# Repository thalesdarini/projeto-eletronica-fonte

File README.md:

# Projeto da Fonte de Tensão

## Objetivos

Projetar uma fonte de tensão ajustável que varie de 3V a 12V e que suporte uma corrente de pelo menos 100mA.

**Aluno:** Thales Darini Souza - 10747562

## Circuito no Falstad
**[Link do circuito no Falstad](http://tinyurl.com/y722ua49)**

**[Link do vídeo explicativo](https://youtu.be/_xOmkor7MkY)**

## Componentes utilizados

|Nome|Especificações|Descrição|Preço|
|---|---|---|---|
|Transformador|12V+12V 300mA|Utilizado para converter a tensão da tomada de 127V AC para 24V AC. Com esses 24V de pico é possível garantir que o zener fique constantemente ligado, considerando as quedas de tensão e ainda com uma boa margem de segurança.|[R$ 16,45](https://www.baudaeletronica.com.br/transformador-trafo-12v-12v-300ma-110-220vac.html)|
|Diodos|1N4001|Utilizados para formar a ponte de diodos a fim de aproveitar ambos os ciclos negativo e positivo da corrente alternada. Juntamente com o capacitor, a ponte retificadora é responsável por transformar a tensão de AC para CC e retificá-la.|[4x R$ 0,14 = R$ 0,56](https://www.baudaeletronica.com.br/diodo-1n4001.html)| 
|Diodo Zener|BZX55C 13V|A função deste zener será manter uma tensão constante de 13V entre seus polos, que, com a ajuda de um potenciômetro, poderá ser ajustada no intervalo de 3V a 12V para a carga, como desejado.|[R$ 0,09](https://www.baudaeletronica.com.br/diodo-zener-bzx55c-13v-0-5w.html)|
|Capacitor Eletrolítico|330uF 35V|O capacitor armazena energia ao longo de cada oscilação para garantir que sempre seja fornecida energia ao restante do circuito. Foi escolhido o de 330uF para a tensão de ~24V provinda do transformador por ser suficiente para manter o zener ligado o tempo todo sem oscilações.|[R$ 0,34](https://www.baudaeletronica.com.br/capacitor-eletrolitico-330uf-35v.html)|
|Potenciômetro|10K|É com o potenciômetro que ajustamos a tensão final fornecida à carga, variando de 3V a 12V.|[R$ 1,46](https://www.baudaeletronica.com.br/potenciometro-linear-de-10k-10000.html)|
|Resistor|2K2 (1/4W)|Este resistor regula a corrente que passa pelo zener, mantendo-a abaixo de 5mA.|[R$ 0,08](https://www.baudaeletronica.com.br/resistor-2k2-5-1-4w.html)|
|Resistor|5K6 (1/4W)|A função deste resistor é limitar a tensão mínima fornecida à carga em 3V quando o potênciometro está no seu limite inferior.|[R$ 0,08](https://www.baudaeletronica.com.br/resistor-5k6-5-1-4w.html)|
|Resistor|560R (1/4W)|Usado para ligar o LED difuso no final do circuito. Especificação do fabricante para uma tensão de 12V.|[R$ 0,08](https://www.baudaeletronica.com.br/resistor-560r-5-1-4w.html)|
|LED difuso|3mm verde|Conectado ao fim do circuito para indicar que a fonte está ligada. Além disso, a intensidade de seu brilho é diretamente proporcional à tensão que passa pela carga, que varia de 3V a 12V.|[R$ 0,24](https://www.baudaeletronica.com.br/led-difuso-3mm-verde.html)|
|Transistor NPN|BC635|Este transistor é usado para manter a tensão desejada de até 12V na carga a partir da tensão provinda do zener e do potenciômetro e, ao mesmo tempo, permitir a passagem da corrente desejada de 100mA.|[R$ 0,33](https://www.baudaeletronica.com.br/transistor-npn-bc635.html)|
|**Total**|||**R$ 19,71**|

## Esquemático no Eagle 

## PCB no Eagle

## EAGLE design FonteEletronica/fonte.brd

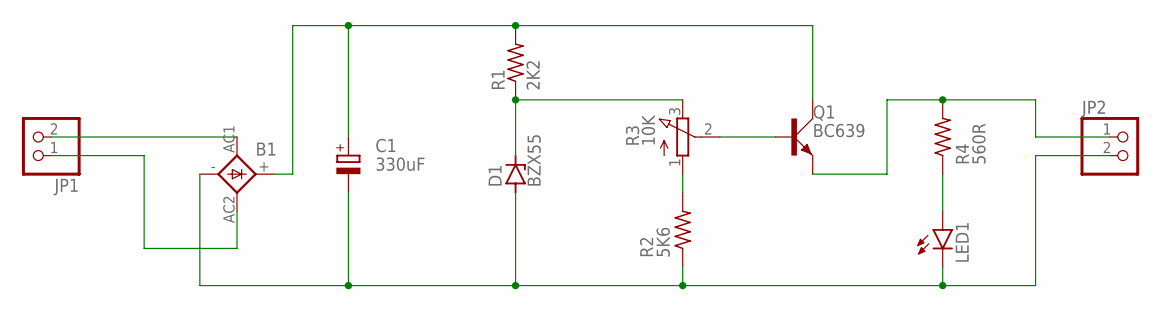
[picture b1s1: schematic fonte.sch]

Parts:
B1: 1KAB
C1: 330uF; E3,5-10
D1: BZX55; DO35Z10
JP1, JP2: PINHD-1X2; 1X02
LED1: LED3MM
Q1: BC639; SOT54D
R1: 2K2; 0309/12
R2: 5K6; 0309/12
R3: 10K; 3RP/1610N
R4: 560R; 0309/12

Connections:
unnamed: B1.AC1, JP1.2
unnamed: B1.AC2, JP1.1
unnamed: B1.+, C1.+, Q1.C, R1.2
unnamed: B1.-, C1.-, D1.A, JP2.2, LED1.K (C), R2.1
unnamed: D1.C, R1.1, R3.3 (E)
unnamed: R2.2, R3.1 (A)
unnamed: Q1.B, R3.2 (S)
unnamed: JP2.1, Q1.E, R4.2
unnamed: LED1.A, R4.1

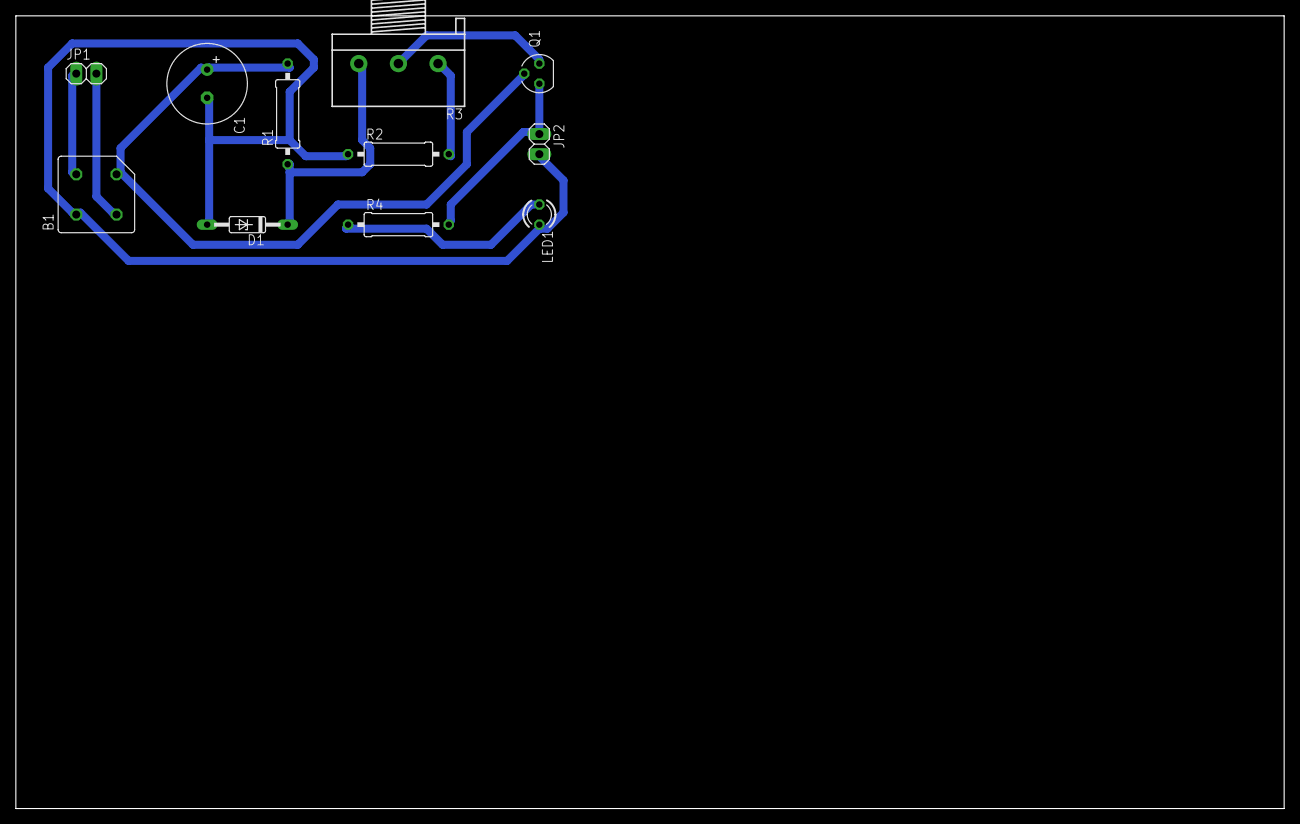
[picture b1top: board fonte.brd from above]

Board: 2 copper layers, 160.0 x 100.0 mm, 11 parts (0 on the bottom side), 9 nets.
